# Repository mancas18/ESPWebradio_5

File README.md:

https://22x22.de/posts/webradio/

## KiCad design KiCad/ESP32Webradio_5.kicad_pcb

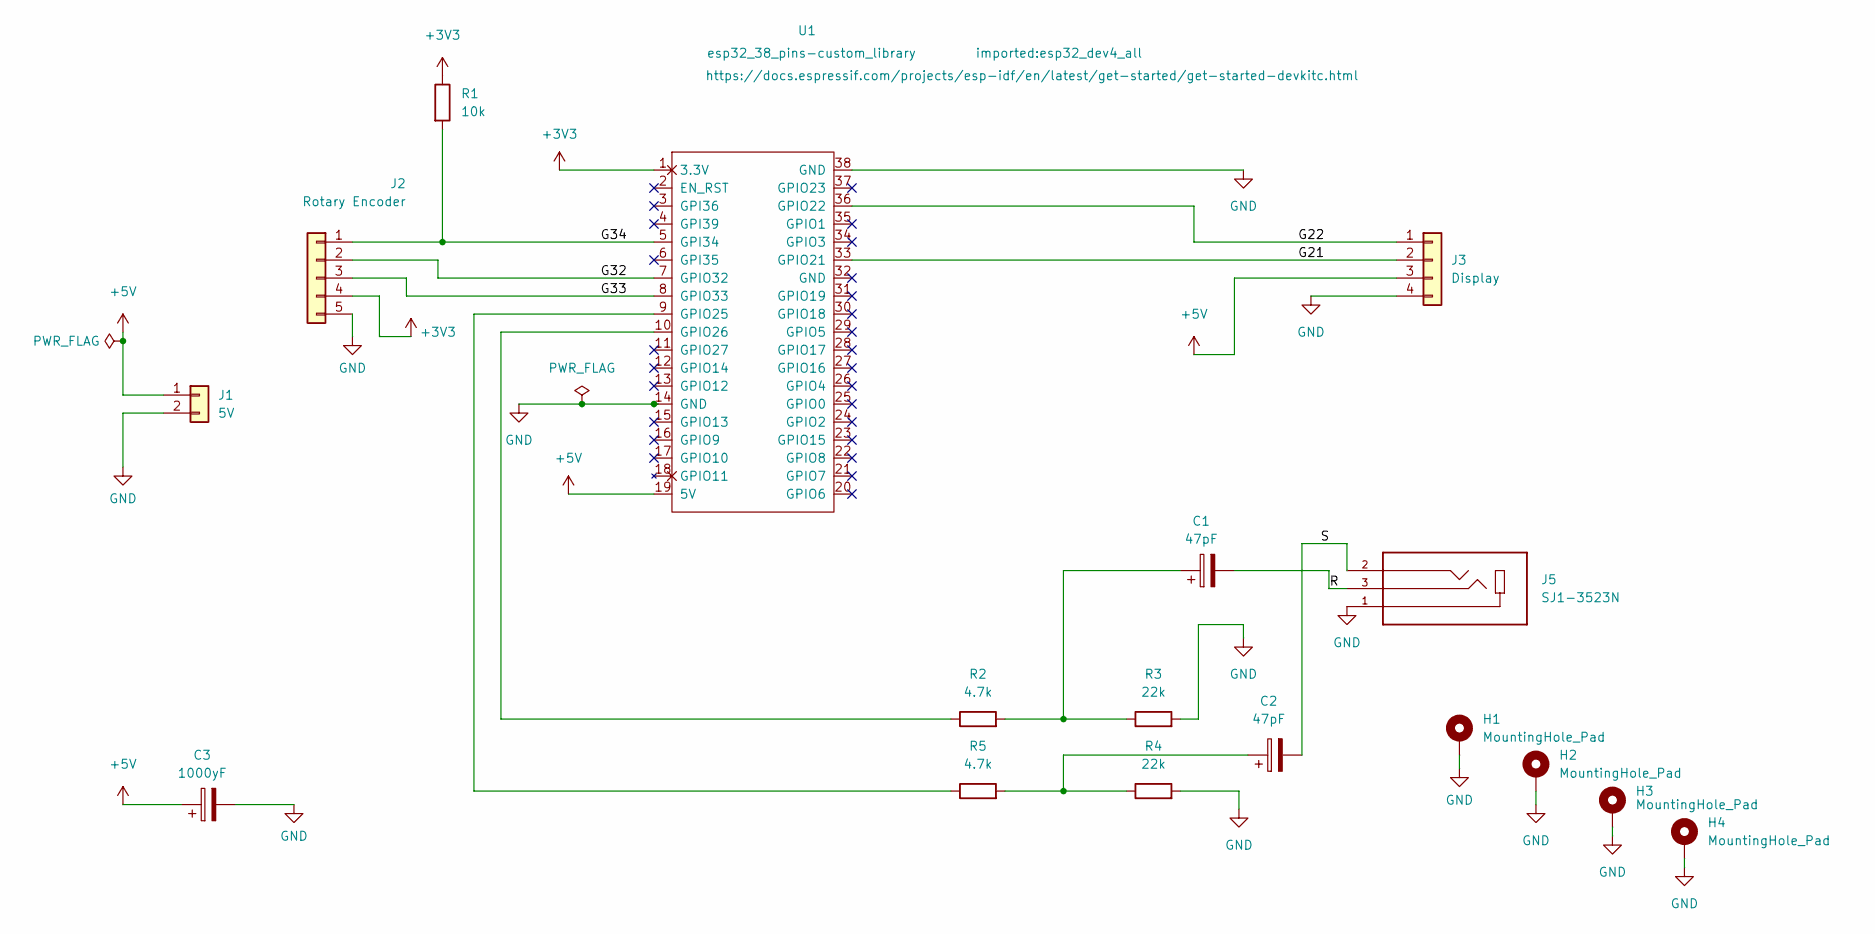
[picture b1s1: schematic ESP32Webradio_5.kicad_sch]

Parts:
C1, C2: 47pF; CP_Radial_D4.0mm_P2.00mm
C3: 1000yF; CP_Radial_D4.0mm_P2.00mm
H1, H2, H3, H4: MountingHole_Pad; MountingHole_3.2mm_M3_DIN965_Pad
J1: 5V; PinHeader_1x02_P2.54mm_Vertical
J2: Rotary Encoder; PinHeader_1x05_P2.54mm_Vertical
J3: Display; PinHeader_1x04_P2.54mm_Vertical
J5: SJ1-3523N; CUI_SJ1-3523N; PARTREV 1.02
R1: 10k; R_Axial_DIN0204_L3.6mm_D1.6mm_P7.62mm_Horizontal
R2, R5: 4.7k; R_Axial_DIN0204_L3.6mm_D1.6mm_P7.62mm_Horizontal
R3, R4: 22k; R_Axial_DIN0204_L3.6mm_D1.6mm_P7.62mm_Horizontal
U1: esp32_38_pins-custom_library; esp32_dev4_all

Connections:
+3V3: J2.4, R1.1, U1.1 (3.3V)
+5V: C3.1, J1.1, J3.3, U1.19 (5V)
/G21: J3.2, U1.33 (GPIO21)
/G22: J3.1, U1.36 (GPIO22)
/G32: J2.2, U1.7 (GPIO32)
/G33: J2.3, U1.8 (GPIO33)
/G34: J2.1, R1.2, U1.5 (GPI34)
/R: C1.2, J5.3
/S: C2.2, J5.2
GND: C3.2, H1.1, H2.1, H3.1, H4.1, J1.2, J2.5, J3.4, J5.1, R3.2, R4.2, U1.14 (GND), U1.38 (GND)
unnamed: C1.1, R2.2, R3.1
unnamed: C2.1, R4.1, R5.2
unnamed: R2.1, U1.10 (GPIO26)
unnamed: R5.1, U1.9 (GPIO25)

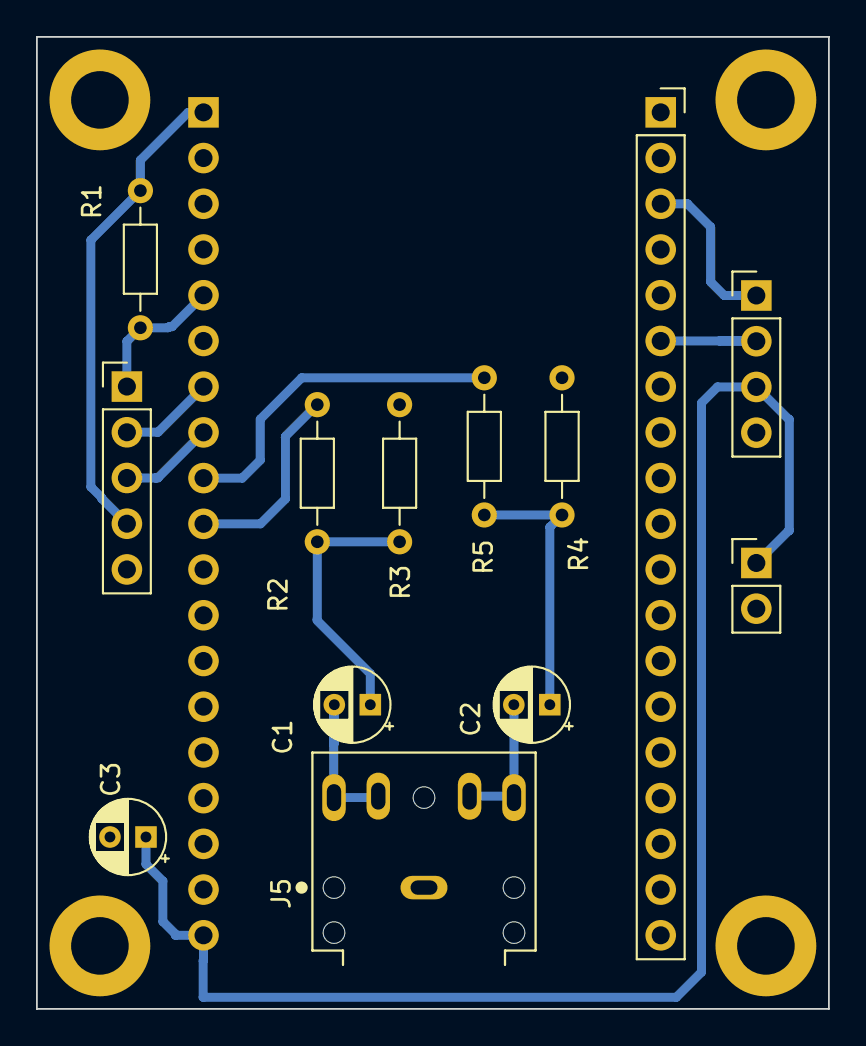
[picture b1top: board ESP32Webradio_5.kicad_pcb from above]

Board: 2 copper layers, 44.0 x 54.0 mm, 17 parts (0 on the bottom side), 14 nets.

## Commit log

2022-06-24 start
2022-06-24 gerber
2022-07-04 upload 3D print files
2022-07-04 upload ESP32 Software
2022-07-05 OLED bracket added
2022-07-05 position of circuit board pillar corrigated
2022-07-05 README
2022-07-06 corrigate restor values
2022-07-07 PCB_Connections file
2022-07-07 cleared directories
2022-07-07 schematic added
